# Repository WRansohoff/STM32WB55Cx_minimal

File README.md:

# STM32WB55 Example Board

**NOTE: I haven't had a chance to test this board much yet, so if you stumble across this, please wait a few weeks before trying to make one!** I'll update the repository with full gerber files and more information once I've checked that the radio/antenna/etc. work. It's my first RF design, so they might not.

I have received a first revision of the boards and verified that the microcontrollers can be programmed with a simple 'blinking LED' application, but I haven't tested any of the advanced peripherals such as USB or Bluetooth. Also, I think that I accidentally reversed the power pins on the USB connector footprint, so it's a good thing that I included a reverse polarity protection diode! That will be fixed shortly, but for now it is a reminder not to order one of these boards yet :)

I've been trying to do a better job of documenting the board designs that I make, so hopefully this can eventually grow into a useful reference design. In the meantime, sorry for the inconvenience and stay tuned.

# Board Renders

I tried to design this so that it could be soldered by hand if you don't have access to PCA services or a reflow station, but the small 0402 parts take a steady hand:

# Future Work

* Obviously, I need to write suitable firmwares to test the radio systems, USB communication, internal switching power supply, etc.

* Instead of using a separate bandpass filter and impedance-matching network, it might be easier to use an integrated filter chip which ST designed for these microcontrollers; part #MLPF-WB55-01E3. It only costs about $0.30, and it seems less error-prone than blindly using the pi filter values from the reference schematics.

* Adding an input button might be a good idea, to extend the range of potential applications.

* I should add a switch or jumper connected to the `BOOT0` pin, because it looks like it is only possible to change or update the co-processor's radio firmware in DFU mode. Fortunately, with the current design, you can remove the 10K resistor on the bottom of the board and solder a jumper between the `BOOT0` side of its pad and the `VDD` side of the 100K resistor which is right next to it. But that's not a good solution.

* Maybe I should move the `SWDIO`, `SWCLK`, and `NRST` pins to the two headers on either side of the board; it's unwieldy to have pin headers overhanging the USB plug.

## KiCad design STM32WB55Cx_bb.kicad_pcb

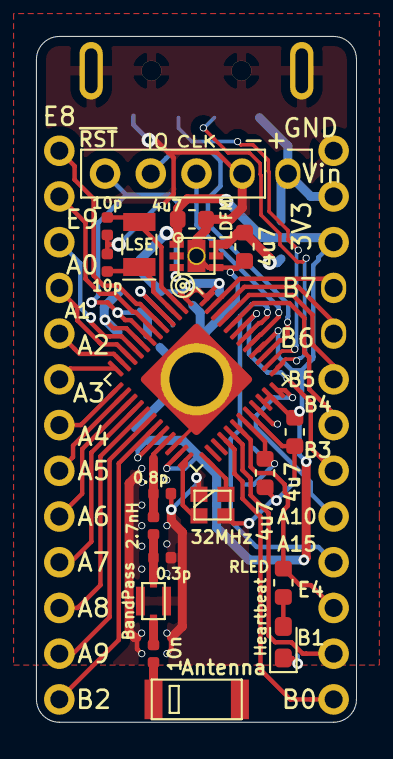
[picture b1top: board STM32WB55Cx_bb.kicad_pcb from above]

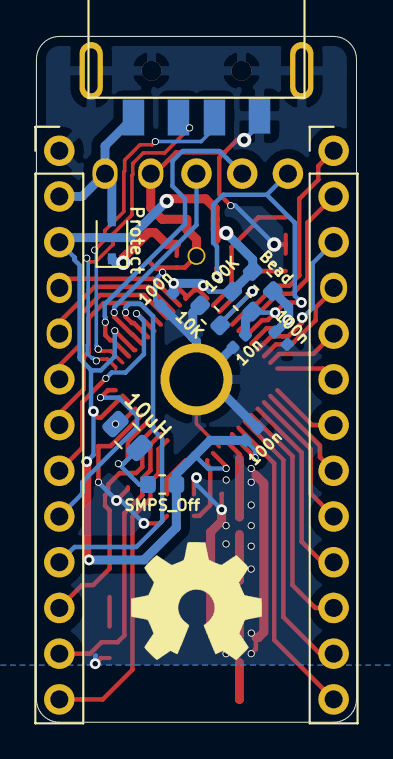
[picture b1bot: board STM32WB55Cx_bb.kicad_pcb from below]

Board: 2 copper layers, 17.8 x 38.1 mm, 32 parts (13 on the bottom side), 45 nets.

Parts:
AE1: Antenna; AA029_BLE-WiFi_Antenna
C1: 0.8p; C_0402_1005Metric
C2: 0.3p; C_0402_1005Metric
C3, C4, C5: 100n; C_0402_1005Metric
C6, C7, C10, C11: 4u7; C_0603_1608Metric
C8, C9: 10p; C_0402_1005Metric
C12, C13: 10n; C_0402_1005Metric
D1: Protect; D_SOD-323
D2: Heartbeat; LED_0603_1608Metric_Pad1.05x0.95mm_HandSolder
FL1: BandPass; LFB21x_SG_Bandpass
J1: Prog; PinHeader_1x05_P2.54mm_Vertical
J2: USB; USBA_Plug_Molex_480372200
J3: GPIO1; PinHeader_1x13_P2.54mm_Vertical
J4: GPIO2; PinHeader_1x13_P2.54mm_Vertical
JP1: SMPS_Off; R_0603_1608Metric
L1: 2.7nH; L_0402_1005Metric
L2: Bead; R_0603_1608Metric
L3: 10uH; L_0805_2012Metric
R1: 10K; R_0603_1608Metric
R2: 100K; R_0603_1608Metric
R3: RLED; R_0603_1608Metric
U1: STM32WB55Cx; QFN-48-1EP_7x7mm_P0.5mm_EP5.3x5.3mm
U2: LDFM; ST_LDFM_2x2DFN
Y1: LSE; Crystal_SMD_EuroQuartz_EQ161-2Pin_3.2x1.5mm
Y2: 32MHz; NX2016_XTal

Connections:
A0: J3.3, U1.9
A1: J3.4, U1.10
A2: J3.5, U1.11
A3: J3.6, U1.12
A4: J3.7, U1.13
A5: J3.8, U1.14
A6: J3.9, U1.15
A7: J3.10, U1.16
A8: J3.11, U1.17
A9: J3.12, U1.18
A10: J4.9, U1.36
A15: J4.10, U1.42
B0: J4.13, U1.28
B1: J4.12, U1.29
B2: J3.13, U1.19
B3: J4.8, U1.43
B4: J4.7, U1.44
B5: J4.6, U1.45
B6: J4.5, U1.46
B7: J4.4, U1.47
BOOT0: R1.2, U1.4
E4: J4.11, R3.1, U1.30
E8: J3.1, U1.5
E9: J3.2, U1.6
GND: C1.1, C2.1, C3.1, C4.1, C5.2, C6.1, C7.1, C8.2, C9.1, C10.1, C11.1, C13.2, D2.1, FL1.2, FL1.4, J1.2, J2.4, J2.5, J4.1, R1.1, U1.22, U1.32, U1.49, U2.4, U2.7, Y2.2
unnamed: AE1.1, C12.1
unnamed: C2.2, FL1.1, L1.2
unnamed: C3.2, L2.2, U1.8
unnamed: C7.2, JP1.1, L3.2, U1.31
unnamed: C8.1, U1.2, Y1.2
unnamed: C9.2, U1.3, Y1.1
unnamed: C12.2, FL1.3
unnamed: D2.2, R3.2
unnamed: L3.1, U1.33
unnamed: U1.24, Y2.1
unnamed: U1.25, Y2.3
RF1: C1.2, L1.1, U1.21
SWCLK: J1.3, U1.41
SWDIO: J1.4, U1.39
USB_D+: J2.3, U1.38
USB_D-: J2.2, U1.37
VAA: C11.2, D1.1, U2.5, U2.6
VDD: C4.2, C5.1, C6.2, C10.2, J4.3, JP1.2, L2.1, R2.1, U1.1, U1.20, U1.23, U1.34, U1.35, U1.40, U1.48, U2.1
VPP: D1.2, J1.1, J2.1, J4.2
~RST: C13.1, J1.5, R2.2, U1.7, U2.3

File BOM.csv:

Part ID,Part type,Part size,Part value,Example Digikey Item,Cost (qty: x),Comment
AE1,Antenna,Custom,Unictron H2U262GKBA0100,https://www.digikey.com/short/p2h8zn,$0.64,"Trace antennas are cheaper, but this seemed like a less failure-prone option for a first attempt."
C1,Capacitor,0402,0.8 pF,https://www.digikey.com/short/p2hrp7,$0.15,"50Ω matching filter capacitor. I used the values from ST's evaluation board, figuring they'd probably be fairly close. Ideal values will vary based on your board stackup. Prefer high-quality ceramic capacitors (C0G/NP0)"
C2,Capacitor,0402,0.3 pF,https://www.digikey.com/short/p2hrjw,$0.19,Another 50Ω matching filter capacitor.
"C3, C4, C5",Capacitor,0402,100 nF,https://www.digikey.com/short/p2hrz2,$0.30,Power supply decoupling capacitors. Prefer X5/X7 ceramic capacitors.
"C6, C7",Capacitor,0603,4.7 μF,https://www.digikey.com/short/p2hdqt,$0.34,SMPS decoupling capacitors for the built-in switching power supply. Prefer X5/X7 ceramic capacitors.
"C8, C9",Capacitor,0402,10 pF,https://www.digikey.com/short/p2hrhj,$0.20,Filtering capacitors for the 32.768KHz 'Low-Speed External' crystal oscillator. Prefer high-quality C0G/NP0 ceramic capacitors.
"C10, C11",Capacitor,0603,4.7 μF,https://www.digikey.com/short/p2hdqt,$0.34,Decoupling capacitors for the 3.3V voltage regulator. Prefer X5/X7 ceramic capacitors.
C12,Capacitor,0402,10 nF,https://www.digikey.com/short/p2hr54,$0.10,Filtering capacitor that sits between the 2.45GHz bandpass filter and the antenna. Prefer X7 ceramic capacitor.
C13,Capacitor,0402,10 nF,https://www.digikey.com/short/p2hr54,$0.10,Decoupling capacitor for the reset line.
D1,Schottky Diode,SOD-323,"20-40V, 0.5-2A",https://www.digikey.com/short/p2hd37,$0.31,Schottky diode to protect against reverse polarity.
D2,LED,0603,Your favorite color,https://www.digikey.com/short/p2hdpf,$0.14,LED indicator connected to pin E4.
FL1,Filter,0805,2.45GHz bandpass,https://www.digikey.com/short/p2hndq,$0.24,Bandpass filter which goes between the 50Ω impedance matching network and the antenna.
J1,Pins or Sockets,"0.1""",1x5,https://www.digikey.com/short/p2hd9v,$0.17,"Programming header; reset, SWDIO, SWCLK, ground, power input. These pin headers are commodities, and it's much chepaer to order them in bulk 1x40 rows."
J2,USB A Plug,-,-,https://www.digikey.com/short/p2hn02,$1.30,"USB-A plug, since the chip has a USB peripheral."
"J3, J4",Pins or Sockets,"0.1""",1x13,https://www.digikey.com/short/p2hdhn,$0.64,"GPIO pin headers, for plugging into a breadboard or socket."
JP1,Jumper,0603,0Ω,https://www.digikey.com/short/p2hdnn,$0.10,Fit a jumper here to disable the internal switching power supply. Requires a corresponding firmware configuration.
L1,Inductor,0402,2.7 nH,https://www.digikey.com/short/p2hn1q,$0.10,"50Ω matching filter inductor. Again, the value is from ST's reference design."
L2,Ferrite Bead,0603,-,https://www.digikey.com/short/p2h080,$0.10,A ferrite bead to filter out high-frequency noise on the analog voltage pin.
L3,Inductor,0805,10 μH,https://www.digikey.com/short/p2h03f,$0.14,Inductor for the internal switching power supply.
R1,Resistor,0603,10 KΩ,https://www.digikey.com/short/p2hddd,$0.10,Pull-down resistor for the 'BOOT0' pin.
R2,Resistor,0603,100 KΩ,https://www.digikey.com/short/p2hd0t,$0.10,"Pull-up resistor for the reset pin. This probably isn't needed since the chips have an internal ~47KΩ pull-up on this pin, but the reference design has a pull-up so I included one."
R3,Resistor,0603,~1 KΩ,https://www.digikey.com/short/p2hdw9,$0.10,Resistor for the LED indicator. Adjust depending on how bright or dim you want the LED to be.
U1,Microcontroller,QFN-48,STM32WB55Cx,https://www.digikey.com/short/p2hd4t,$6.65,Core microcontroller; available with either 512KB or 1MB of Flash memory.
U2,Voltage Regulator,DFN-6,LFDM33PVR,https://www.digikey.com/short/p2hdm4,$0.75,500mA low-dropout linear voltage regulator.
Y1,Crystal,3.2x1.5mm,32.768KHz,https://www.digikey.com/short/p2h0zh,$0.41,Low-Speed External' crystal oscillator.
Y2,Crystal,2.0x1.6mm,32MHz,https://www.digikey.com/short/p2hdhc,$0.64,High-Speed External' crystal oscillator.
Total:,-,-,-,-,$14.35,-

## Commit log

2019-09-26 Add library files for the schematic symbols and footprints.
2019-09-26 Add library table files
2019-09-26 Add project, schematic, and PCB files.
2019-09-26 Add readme file.
2019-09-26 Add board renderings to the readme.
2019-09-26 Add bill of materials CSV file
2019-09-27 Minor silkscreen changes; make pin numbers more legible, and add an OSHW logo on the bottom.
2019-10-07 Update Readme now that I've had the chance to assemble a board and poke at it a bit.
2019-10-21 Fix the USB plug so that it's pinout is not reversed. And to avoid changing the board design too much, flip the USB plug to the bottom of the board.
2019-12-20 Add initial test firmware readme, license, supporting files.
2019-12-20 Add makefile, linker script, vector table for the STM32WB55CE chip (48-QFP, 512KB Flash).
2019-12-20 Add core 'blinking LED' application code.
2019-12-21 Add support files for test USB/serial firmware. (The common files like device headers and the linker script should really go one directory up...)
2019-12-21 Add supporting project files; a simple starter HAL/BSP interface, linker script, and vector table.
2019-12-21 Add core project source/header files.
2019-12-21 Add some more detail to the 'current status' readme section.
2019-12-21 Add a list of to-do items.
2019-12-22 Update memcpy/memset so that lengths are not /4.
2019-12-22 Fix USB_VSP project memcpy/memset calls.
2019-12-22 Add a simple ringbuffer implementation to the USB_VSP project.
2019-12-23 'vcp' -> 'vsp' ('COM' makes less sense than 'Serial')
2019-12-23 Start work on USB peripheral setup.
2019-12-23 Clear power-down bit before performing an internal peripheral reset, as recommended by the reference manual.
2019-12-23 Start on endpoint setup within the USB peripheral.
